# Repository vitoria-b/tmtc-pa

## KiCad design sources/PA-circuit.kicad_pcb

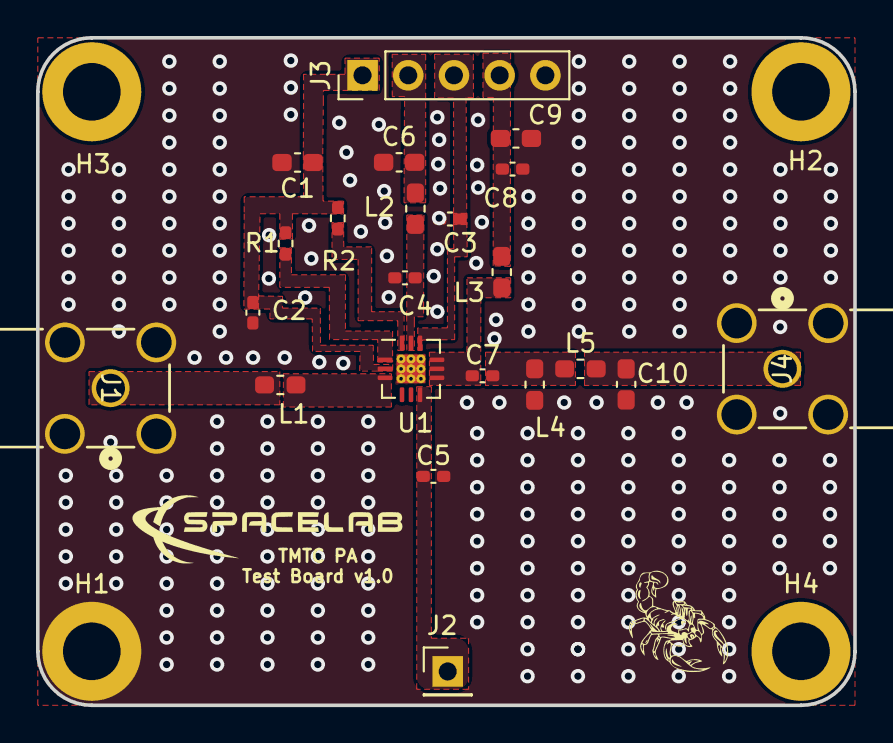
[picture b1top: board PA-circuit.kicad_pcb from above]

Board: 2 copper layers, 45.4 x 37.1 mm, 26 parts (0 on the bottom side), 14 nets, no tracks yet.

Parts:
C1, C6: 1 uF; C_0603_1608Metric_Pad1.08x0.95mm_HandSolder
C2, C3, C5: 100 pF; C_0402_1005Metric_Pad0.74x0.62mm_HandSolder
C4: 2.4 pF; C_0402_1005Metric_Pad0.74x0.62mm_HandSolder
C7: 220 pF; C_0402_1005Metric_Pad0.74x0.62mm_HandSolder
C8: 1000 pF; C_0402_1005Metric_Pad0.74x0.62mm_HandSolder
C9: 4.7 uF; C_0603_1608Metric_Pad1.08x0.95mm_HandSolder
C10: 18 pF; C_0603_1608Metric_Pad1.08x0.95mm_HandSolder
H1: MountingHole_Pad; MountingHole_3.2mm_M3_ISO14580_Pad
H2, H3, H4: MountingHole; MountingHole_3.2mm_M3_ISO14580_Pad
J1, J4: 2484782-1; 2016504-1
J2: Conn_01x01_Female; PinHeader_1x01_P2.54mm_Vertical
J3: Conn_01x05; PinHeader_1x05_P2.54mm_Vertical
L1: 3.9 nH; L_0603_1608Metric_Pad1.05x0.95mm_HandSolder
L2, L5: 5.6 nH; L_0603_1608Metric_Pad1.05x0.95mm_HandSolder
L3: 12 nH; L_0603_1608Metric_Pad1.05x0.95mm_HandSolder
L4: 22 nH; L_0603_1608Metric_Pad1.05x0.95mm_HandSolder
R1: 1.8K 1/16 W; R_0402_1005Metric_Pad0.72x0.64mm_HandSolder
R2: 2K 1/16 W; R_0402_1005Metric_Pad0.72x0.64mm_HandSolder
U1: MMZ09332BT1; QFN-12-1EP_3x3mm_P0.5mm_EP1.6x1.6mm_ThermalVias

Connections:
/Pdc: C3.1, J3.3, U1.10 (POWER_DOWN)
/Pdet: C5.1, J2.1, U1.6 (PDET)
/RF_IN_PA: J1.1, L1.1
/RF_OUT_PA: C10.1, J4.1, L5.2
/Vbias: C1.1, C2.1, J3.1, R1.1, R2.1, U1.2 (VBIAS)
/Vcc1: C6.2, J3.2, L2.1
/Vcc2: C8.1, C9.1, J3.4, L3.2
GNDREF: C1.2, C2.2, C3.2, C4.1, C5.2, C6.1, C8.2, C9.2, C10.2, H1.1, J1.2, J1.3, J1.4, J1.5, J3.5, J4.2, J4.3, J4.4, J4.5, L4.2, U1.13 (GND)
unnamed: C7.1, L3.1, U1.7 (VCC2/RFOUT), U1.8 (VCC2/RFOUT), U1.9 (VCC2/RFOUT)
unnamed: C7.2, L4.1, L5.1
unnamed: L1.2, U1.3 (RF_IN)
unnamed: R1.2, U1.1 (VBA1)
unnamed: R2.2, U1.12 (VBA2)
unnamed: C4.2, L2.2, U1.11 (VCC1)

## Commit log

2025-02-11 updating library
2025-02-11 adding schematics
2025-02-11 developing board layout
2025-02-11 configurating drawing sheets
2025-02-11 adding kicad project
2025-02-11 images folder
2025-02-11 moved or deleted files
2025-02-11 adding design rules based on PCBWay specs
2025-02-11 organizing files order
2025-02-11 fixing designations
2025-02-13 updating rf connector and lib
2025-02-13 outputs files
2025-05-27 adding fabrication files
2025-05-27 finishing layout
